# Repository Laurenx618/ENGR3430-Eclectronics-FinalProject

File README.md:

# ENGR3430-Eclectronics-FinalProject

## Description

This project is for the Eclectronics Final.

The final layout used was `no_connector`.

Here, we have a RPI2040 to connect to an ESP32-WROOM-32 (just for WIFI use) as well as an LCD screen in order to  connect to the internet, read someone's *Now Playing* information using the Spotify API Spotipy, and display the song on the screen. There is also a circuit for light detection, which is used to create a "light" and "dark" mode on screen. All of these are communicating with the RPI2040.

----
## Hardware Connections

* Microcontroller: RPI2040
* WiFi Module: ESP32-WROOM-32
* LCD Screen: 16x2 Serial LCD [(Amazon Link)](https://www.amazon.com/HiLetgo-HD44780-I2C1602-Interface-Backlight/dp/B07W5KC65S)

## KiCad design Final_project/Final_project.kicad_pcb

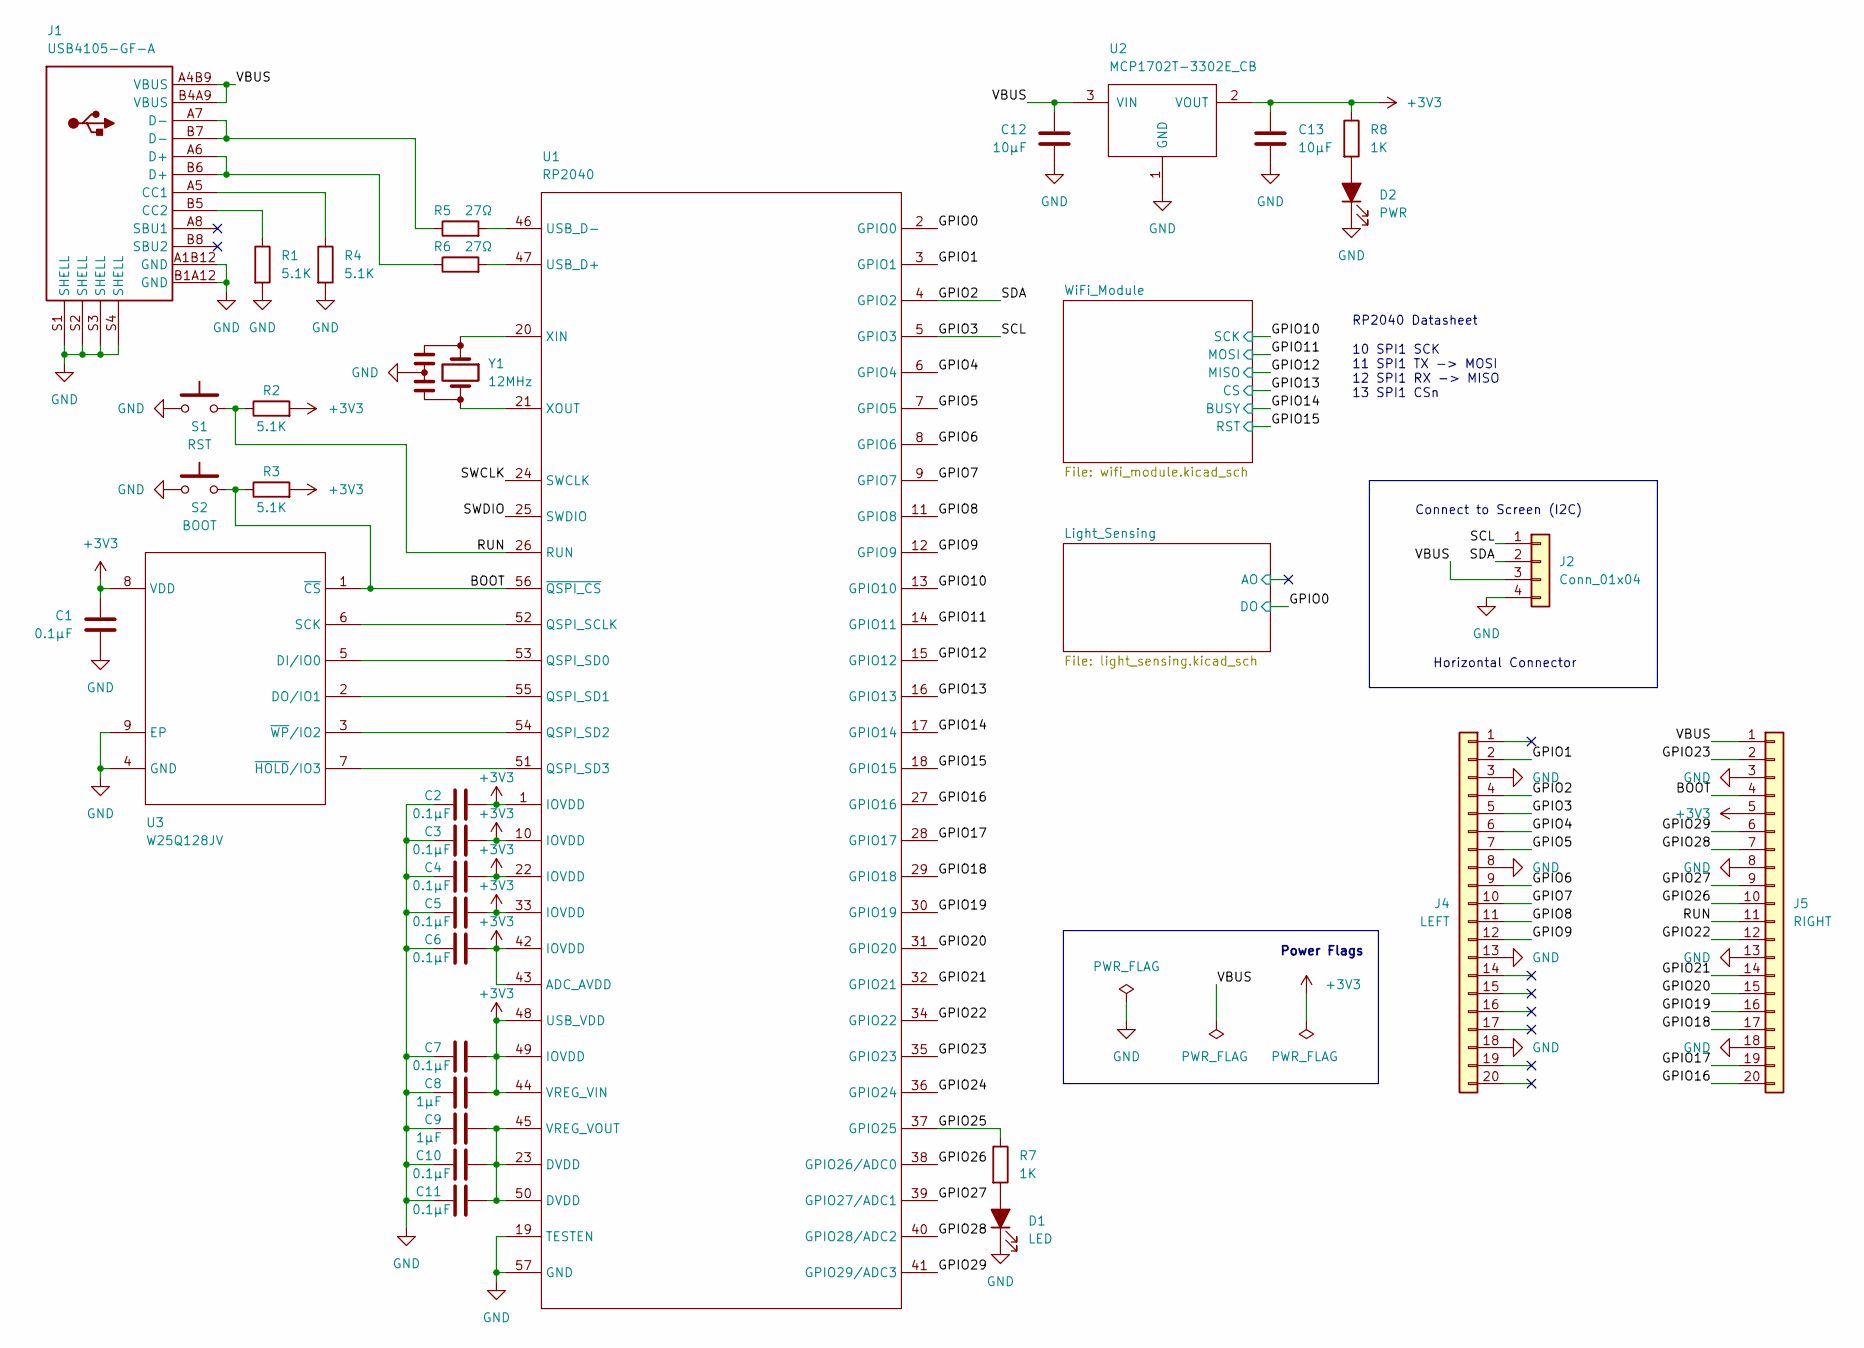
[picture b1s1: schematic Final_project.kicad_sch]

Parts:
C1, C2, C3: 0.1µF; C_0603_1608Metric; Digi-Key_Part CL10B104JB8NNNC
C4, C5, C6, C7, C10, C11: 0.1µF; C_0603_1608Metric
C8: 1µF; C_0603_1608Metric; Digi-Key_Part CL10B105KA8NNNC
C9: 1µF; C_0603_1608Metric
C12, C13: 10µF; C_0603_1608Metric; Digi-Key_Part GRM188R61E106KA73D
D1: LED; LTST-C170TBKT
D2: PWR; LTST-C170TGKT
J1: USB4105-GF-A
J2: Conn_01x04; PinSocket_1x04_P2.54mm_Horizontal
J4: LEFT; PinSocket_1x20_P2.54mm_Vertical
J5: RIGHT; PinSocket_1x20_P2.54mm_Vertical
R1: 5.1K; R_0603_1608Metric
R2, R4: 5.1K; R_0603_1608Metric; Digi-Key_Part ERJ-3EKF5101V
R3: 5.1K; R_0603_1608Metric; Digi-Key_Part ERJ-3EKF5101VERJ-3EKF5101V
R5: 27Ω; R_0603_1608Metric; Part RC0603FR-071KL
R6: 27Ω; R_0603_1608Metric
R7, R8: 1K; R_0603_1608Metric; Digi-Key_Part RC0603FR-071KL
S1: RST; KXT321LHS
S2: BOOT; KXT321LHS
U1: RP2040
U2: MCP1702T-3302E_CB; MCP1702T-3302E&slash_CB
U3: W25Q128JV; MIC_WSON-8-M
Y1: 12MHz; CSTNE

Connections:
+3V3: C1.2, C2.1, C3.1, C4.1, C5.1, C6.1, C7.1, C8.1, C13.1, J5.5, R2.2, R3.2, R8.1, U1.1 (IOVDD), U1.10 (IOVDD), U1.22 (IOVDD), U1.33 (IOVDD), U1.42 (IOVDD), U1.43 (ADC_AVDD), U1.44 (VREG_VIN), U1.48 (USB_VDD), U1.49 (IOVDD), U2.2 (VOUT), U3.8 (VDD); also elsewhere on the board
/BOOT: J5.4, R3.1, S2.2, U1.56 (~QSPI_CS), U3.1 (~CS)
/GPIO0: U1.2 (GPIO0); also elsewhere on the board
/GPIO1: J4.2, U1.3 (GPIO1)
/GPIO2: J2.2, J4.4, U1.4 (GPIO2)
/GPIO3: J2.1, J4.5, U1.5 (GPIO3)
/GPIO4: J4.6, U1.6 (GPIO4)
/GPIO5: J4.7, U1.7 (GPIO5)
/GPIO6: J4.9, U1.8 (GPIO6)
/GPIO7: J4.10, U1.9 (GPIO7)
/GPIO8: J4.11, U1.11 (GPIO8)
/GPIO9: J4.12, U1.12 (GPIO9)
/GPIO10: U1.13 (GPIO10); also elsewhere on the board
/GPIO11: U1.14 (GPIO11); also elsewhere on the board
/GPIO12: U1.15 (GPIO12); also elsewhere on the board
/GPIO13: U1.16 (GPIO13); also elsewhere on the board
/GPIO14: U1.17 (GPIO14); also elsewhere on the board
/GPIO15: U1.18 (GPIO15); also elsewhere on the board
/GPIO16: J5.20, U1.27 (GPIO16)
/GPIO17: J5.19, U1.28 (GPIO17)
/GPIO18: J5.17, U1.29 (GPIO18)
/GPIO19: J5.16, U1.30 (GPIO19)
/GPIO20: J5.15, U1.31 (GPIO20)
/GPIO21: J5.14, U1.32 (GPIO21)
/GPIO22: J5.12, U1.34 (GPIO22)
/GPIO23: J5.2, U1.35 (GPIO23)
/GPIO24: U1.36 (GPIO24)
/GPIO25: R7.1, U1.37 (GPIO25)
/GPIO26: J5.10, U1.38 (GPIO26/ADC0)
/GPIO27: J5.9, U1.39 (GPIO27/ADC1)
/GPIO28: J5.7, U1.40 (GPIO28/ADC2)
/GPIO29: J5.6, U1.41 (GPIO29/ADC3)
/RUN: J5.11, R2.1, S1.2, U1.26 (RUN)
/SWCLK: U1.24 (SWCLK)
/SWDIO: U1.25 (SWDIO)
/VBUS: C12.2, J1.A4B9 (VBUS), J1.B4A9 (VBUS), J2.3, J5.1, U2.3 (VIN)
GND: C1.1, C2.2, C3.2, C4.2, C5.2, C6.2, C7.2, C8.2, C9.2, C10.2, C11.2, C12.1, C13.2, D1.1 (K), D2.1 (K), J1.A1B12 (GND), J1.B1A12 (GND), J1.S1 (SHELL), J1.S2 (SHELL), J1.S3 (SHELL), J1.S4 (SHELL), J2.4, J4.3, J4.8, J4.13, J4.18, J5.3, J5.8, J5.13, J5.18, R1.2, R4.2, S1.1, S2.1, U1.19 (TESTEN), U1.57 (GND), U2.1 (GND), U3.4 (GND), U3.9 (EP), Y1.2; also elsewhere on the board
unnamed: C9.1, C10.1, C11.1, U1.23 (DVDD), U1.45 (VREG_VOUT), U1.50 (DVDD)
unnamed: D1.2 (A), R7.2
unnamed: D2.2 (A), R8.2
unnamed: J1.A5 (CC1), R4.1
unnamed: J1.A6 (D+), J1.B6 (D+), R6.1
unnamed: J1.A7 (D-), J1.B7 (D-), R5.1
unnamed: J1.B5 (CC2), R1.1
unnamed: R5.2, U1.46 (USB_D-)
unnamed: R6.2, U1.47 (USB_D+)
unnamed: U1.20 (XIN), Y1.1
unnamed: U1.21 (XOUT), Y1.3
unnamed: U1.51 (QSPI_SD3), U3.7 (~HOLD/IO3)
unnamed: U1.52 (QSPI_SCLK), U3.6 (SCK)
unnamed: U1.53 (QSPI_SD0), U3.5 (DI/IO0)
unnamed: U1.54 (QSPI_SD2), U3.3 (~WP/IO2)
unnamed: U1.55 (QSPI_SD1), U3.2 (DO/IO1)

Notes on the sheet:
Connect to Screen (I2C)
Horizontal Connector
Power Flags
RP2040 Datasheet 10 SPI1 SCK 11 SPI1 TX -> MOSI 12 SPI1 RX -> MISO 13 SPI1 CSn

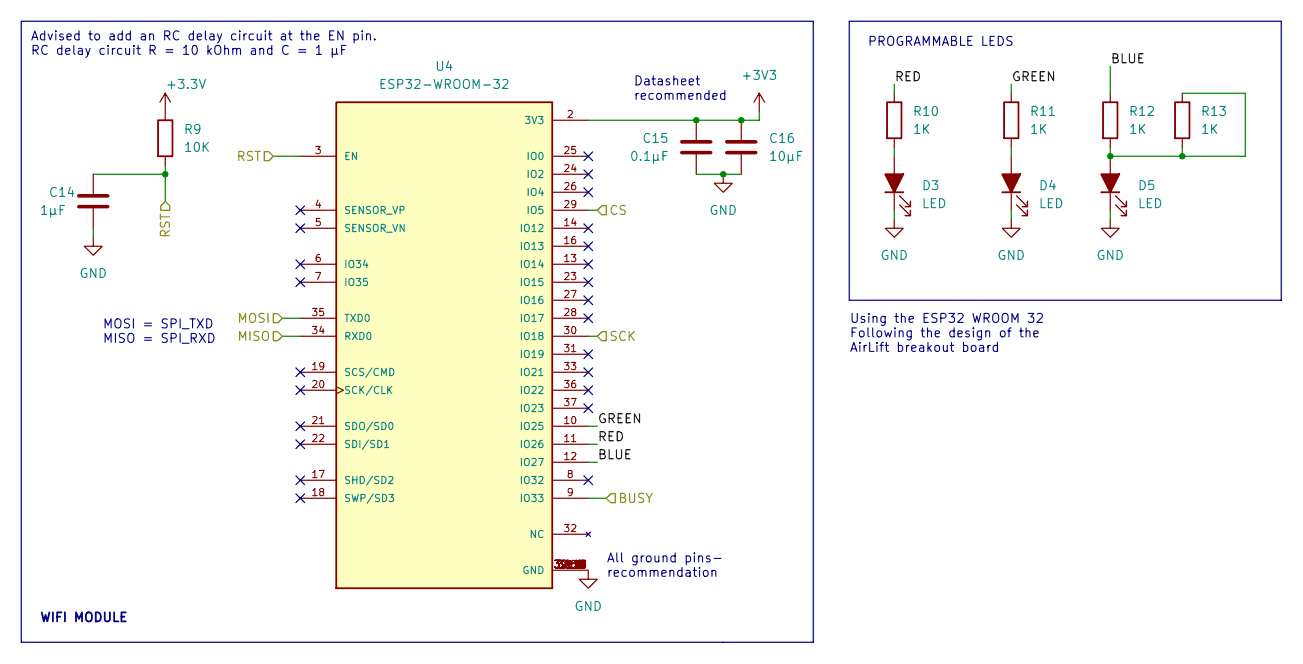
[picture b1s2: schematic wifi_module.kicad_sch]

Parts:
C14: 1µF; C_0603_1608Metric; Digi-Key_Part CL10B105KA8NNNC
C15: 0.1µF; C_0603_1608Metric; Digi-Key_Part CL10B105KA8NNNC
C16: 10µF; C_0603_1608Metric; Digi-Key_Part GRM188R61E106KA73D
D3, D4, D5: LED; LTST-C170TBKT
R9: 10K; R_0805_2012Metric
R10, R11, R12: 1K; R_0603_1608Metric; Digi-Key_Part RC0603FR-071KL
R13: 1K; R_0603_1608Metric
U4: ESP32-WROOM-32; MODULE_ESP32-WROOM-32; PARTREV 2.9

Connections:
+3.3V: R9.1
+3V3: C15.1, C16.1, U4.2 (3V3); also elsewhere on the board
/GPIO10: U4.30 (IO18); also elsewhere on the board
/GPIO11: U4.35 (TXD0); also elsewhere on the board
/GPIO12: U4.34 (RXD0); also elsewhere on the board
/GPIO13: U4.29 (IO5); also elsewhere on the board
/GPIO14: U4.9 (IO33); also elsewhere on the board
/GPIO15: C14.2, R9.2, U4.3 (EN); also elsewhere on the board
/WiFi_Module/BLUE: R12.1, U4.12 (IO27)
/WiFi_Module/GREEN: R11.1, U4.10 (IO25)
/WiFi_Module/RED: R10.1, U4.11 (IO26)
GND: C14.1, C15.2, C16.2, D3.1 (K), D4.1 (K), D5.1 (K), U4.1 (GND), U4.15 (GND), U4.38 (GND), U4.39_1 (GND), U4.39_2 (GND), U4.39_3 (GND), U4.39_4 (GND), U4.39_5 (GND), U4.39_6 (GND), U4.39_7 (GND), U4.39_8 (GND), U4.39_9 (GND), U4.39_10 (GND), U4.39_11 (GND), U4.39_12 (GND), U4.39_13 (GND), U4.39_14 (GND), U4.39_15 (GND), U4.39_16 (GND), U4.39_17 (GND), U4.39_18 (GND), U4.39_19 (GND), U4.39_20 (GND), U4.39_21 (GND); also elsewhere on the board
unnamed: D3.2 (A), R10.2
unnamed: D4.2 (A), R11.2
unnamed: D5.2 (A), R12.2, R13.1, R13.2

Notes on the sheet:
PROGRAMMABLE LEDS
WIFI MODULE
All ground pins- recommendation
Datasheet recommended
MOSI = SPI_TXD MISO = SPI_RXD
Using the ESP32 WROOM 32 Following the design of the AirLift breakout board
Advised to add an RC delay circuit at the EN pin. RC delay circuit R = 10 kOhm and C = 1 μF

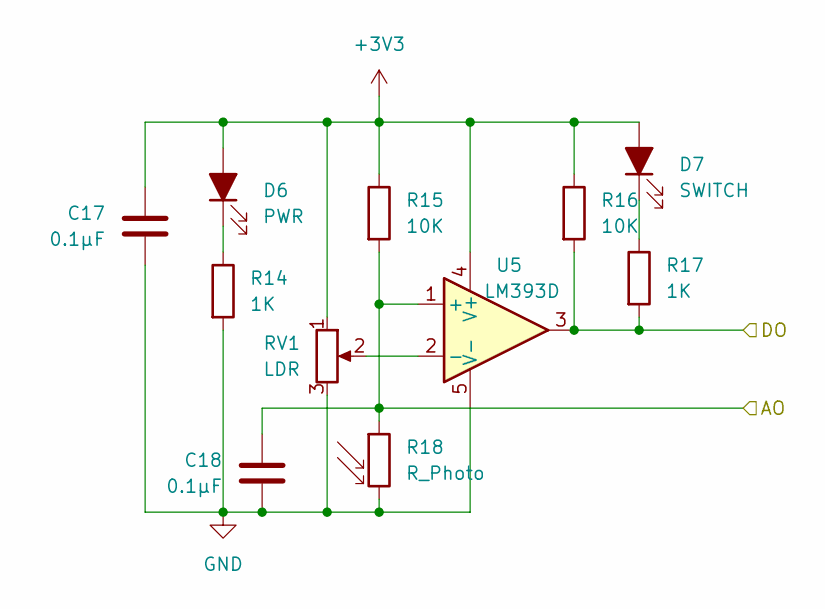
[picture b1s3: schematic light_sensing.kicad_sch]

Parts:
C17, C18: 0.1µF; C_0603_1608Metric; Digi-Key_Part CL10B104JB8NNNC
D6: PWR; LTST-C170TGKT
D7: SWITCH; LTST-C170TGKT
R14, R17: 1K; R_0603_1608Metric; Digi-Key_Part RC0603FR-071KL
R15, R16: 10K; R_0805_2012Metric
R18: R_Photo; 02-LDR4
RV1: LDR; TRIM_T73YU103KT20
U5: LM393D

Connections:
+3V3: C17.2, D6.2 (A), D7.2 (A), R15.1, R16.1, RV1.1, U5.4 (V+); also elsewhere on the board
/GPIO0: R16.2, R17.2, U5.3; also elsewhere on the board
/Light_Sensing/AO: C18.2, R15.2, R18.1, U5.1 (+)
GND: C17.1, C18.1, R14.2, R18.2, RV1.3, U5.5 (V-); also elsewhere on the board
unnamed: D6.1 (K), R14.1
unnamed: D7.1 (K), R17.1
unnamed: RV1.2, U5.2 (-)

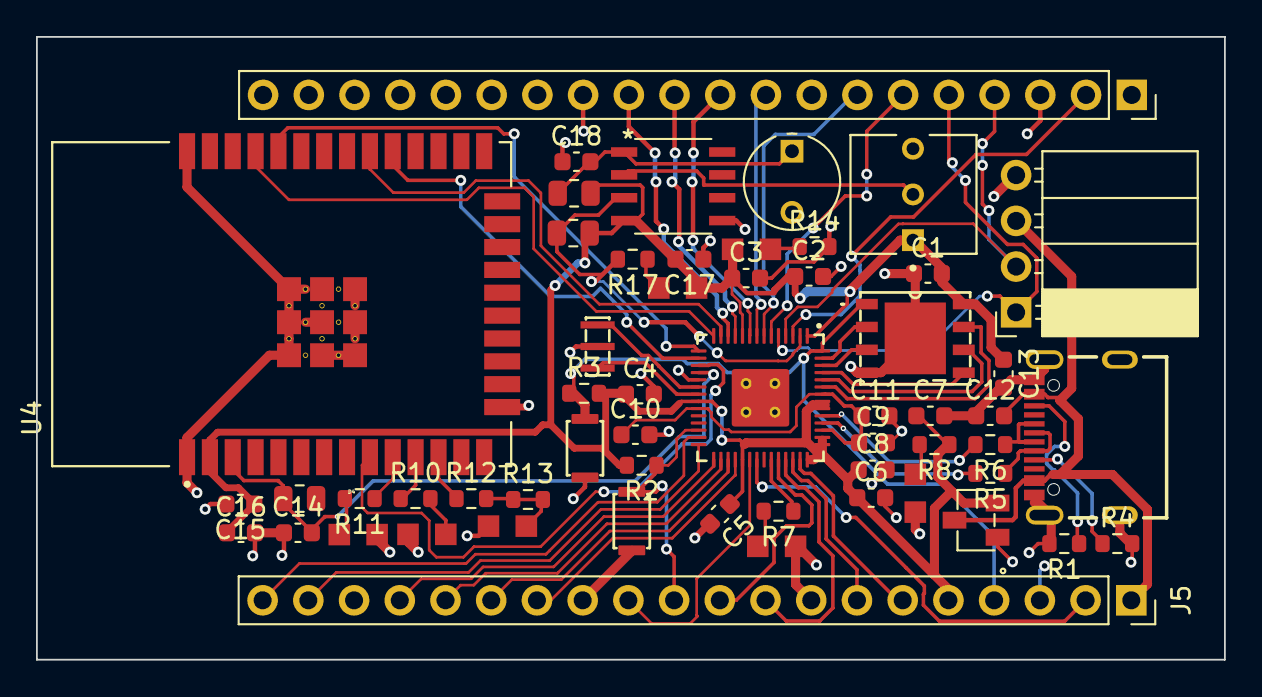
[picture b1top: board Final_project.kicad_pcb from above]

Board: 2 copper layers, 66.0 x 34.6 mm, 56 parts (0 on the bottom side), 60 nets.

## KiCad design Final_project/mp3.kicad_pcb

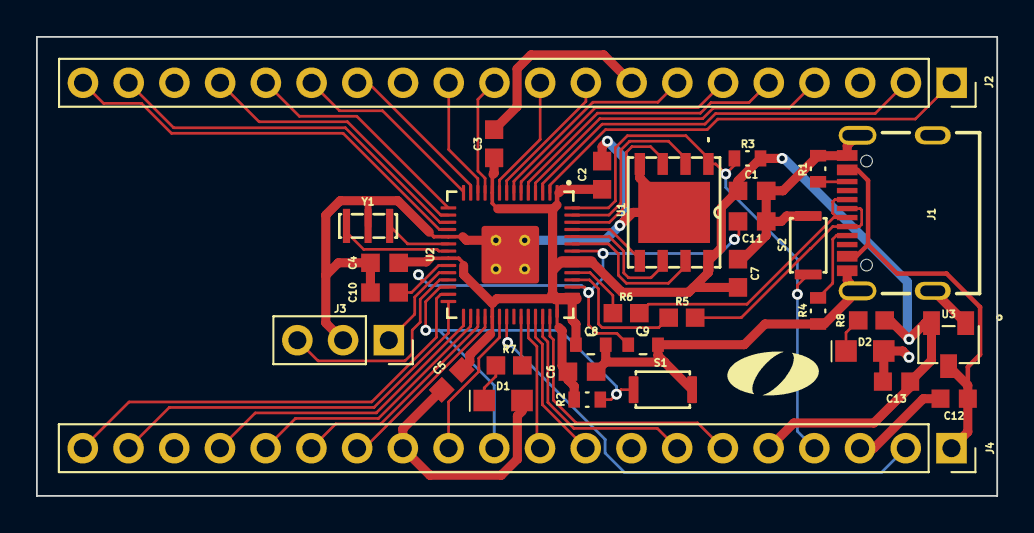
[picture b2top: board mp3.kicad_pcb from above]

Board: 2 copper layers, 53.3 x 25.5 mm, 34 parts (0 on the bottom side), 52 nets.

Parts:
C1, C2, C3, C4, C5, C6, C7, C10, C11: 0.1µF; CL10B104JB8NNNC
C8, C9: 1µF; CL10B105KA8NNNC
C12, C13: 10µF; GRM188R61E106KA73D
D1: LED; LTST-C170TBKT
D2: PWR; LTST-C170TGKT
J1: USB4105-GF-A
J2: LEFT; PinSocket_1x20_P2.54mm_Vertical
J3: DEBUG; PinSocket_1x03_P2.54mm_Vertical
J4: RIGHT; PinSocket_1x20_P2.54mm_Vertical
OlinLogoSm: G***; OlinLogoSm
R1, R2, R3, R4: 5.1K; RES_ERJ3EKF5101V
R5, R6: 27Ω; RC0603FR-071KL
R7, R8: 1K; RC0603FR-071KL
S1: RST; KXT321LHS
S2: BOOT; KXT321LHS
U1: W25Q128JV; MIC_WSON-8-M
U2: RP2040
U3: MCP1702T-3302E_CB; MCP1702T-3302E&slash_CB
Y1: 12MHz; CSTNE

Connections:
+3V3: C1.2, C2.1, C3.1, C4.1, C5.1, C6.1, C7.1, C8.1, C13.1, J4.5, R2.2, R3.2, R8.1, U1.8 (VDD), U2.1 (IOVDD), U2.10 (IOVDD), U2.22 (IOVDD), U2.33 (IOVDD), U2.42 (IOVDD), U2.43 (ADC_AVDD), U2.44 (VREG_VIN), U2.48 (USB_VDD), U2.49 (IOVDD), U3.2 (VOUT)
/BOOT: J4.4, R3.1, S2.2, U1.1 (~CS), U2.56 (~QSPI_CS)
/GPIO0: J2.1, U2.2 (GPIO0)
/GPIO1: J2.2, U2.3 (GPIO1)
/GPIO2: J2.4, U2.4 (GPIO2)
/GPIO3: J2.5, U2.5 (GPIO3)
/GPIO4: J2.6, U2.6 (GPIO4)
/GPIO5: J2.7, U2.7 (GPIO5)
/GPIO6: J2.9, U2.8 (GPIO6)
/GPIO7: J2.10, U2.9 (GPIO7)
/GPIO8: J2.11, U2.11 (GPIO8)
/GPIO9: J2.12, U2.12 (GPIO9)
/GPIO10: J2.14, U2.13 (GPIO10)
/GPIO11: J2.15, U2.14 (GPIO11)
/GPIO12: J2.16, U2.15 (GPIO12)
/GPIO13: J2.17, U2.16 (GPIO13)
/GPIO14: J2.19, U2.17 (GPIO14)
/GPIO15: J2.20, U2.18 (GPIO15)
/GPIO16: J4.20, U2.27 (GPIO16)
/GPIO17: J4.19, U2.28 (GPIO17)
/GPIO18: J4.17, U2.29 (GPIO18)
/GPIO19: J4.16, U2.30 (GPIO19)
/GPIO20: J4.15, U2.31 (GPIO20)
/GPIO21: J4.14, U2.32 (GPIO21)
/GPIO22: J4.12, U2.34 (GPIO22)
/GPIO23: J4.2, U2.35 (GPIO23)
/GPIO25: R7.1, U2.37 (GPIO25)
/GPIO26: J4.10, U2.38 (GPIO26/ADC0)
/GPIO27: J4.9, U2.39 (GPIO27/ADC1)
/GPIO28: J4.7, U2.40 (GPIO28/ADC2)
/GPIO29: J4.6, U2.41 (GPIO29/ADC3)
/RUN: J4.11, R2.1, S1.2, U2.26 (RUN)
/SWCLK: J3.1, U2.24 (SWCLK)
/SWDIO: J3.3, U2.25 (SWDIO)
/VBUS: C12.2, J1.A4B9 (VBUS), J1.B4A9 (VBUS), J4.1, U3.3 (VIN)
GND: C1.1, C2.2, C3.2, C4.2, C5.2, C6.2, C7.2, C8.2, C9.2, C10.2, C11.2, C12.1, C13.2, D1.1 (K), D2.1 (K), J1.A1B12 (GND), J1.B1A12 (GND), J1.S1 (SHELL), J1.S2 (SHELL), J1.S3 (SHELL), J1.S4 (SHELL), J2.3, J2.8, J2.13, J2.18, J3.2, J4.3, J4.8, J4.13, J4.18, R1.2, R4.2, S1.1, S2.1, U1.4 (GND), U1.9 (EP), U2.19 (TESTEN), U2.57 (GND), U3.1 (GND), Y1.2
unnamed: C9.1, C10.1, C11.1, U2.23 (DVDD), U2.45 (VREG_VOUT), U2.50 (DVDD)
unnamed: D1.2 (A), R7.2
unnamed: D2.2 (A), R8.2
unnamed: J1.A5 (CC1), R4.1
unnamed: J1.A6 (D+), J1.B6 (D+), R6.1
unnamed: J1.A7 (D-), J1.B7 (D-), R5.1
unnamed: J1.B5 (CC2), R1.1
unnamed: R5.2, U2.46 (USB_D-)
unnamed: R6.2, U2.47 (USB_D+)
unnamed: U1.2 (DO/IO1), U2.55 (QSPI_SD1)
unnamed: U1.3 (~WP/IO2), U2.54 (QSPI_SD2)
unnamed: U1.5 (DI/IO0), U2.53 (QSPI_SD0)
unnamed: U1.6 (SCK), U2.52 (QSPI_SCLK)
unnamed: U1.7 (~HOLD/IO3), U2.51 (QSPI_SD3)
unnamed: U2.20 (XIN), Y1.1
unnamed: U2.21 (XOUT), Y1.3

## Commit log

2022-11-16 Add library and hierarchical schematic
2022-11-16 added audiojack
2022-11-18 Complete wifi module airlift
2022-11-18 Complete pinouts on main
2022-11-18 assigned footprints to audiojack caps
2022-11-18 Add light sensing sheet
2022-11-26 Add miniproj parts, begin photosensing circuit
2022-11-26 added copy of light sensing module
2022-11-27 Add pinouts for connectors
2022-11-27 added a footprint to the current library and uploaded Micropython_code
2022-11-27 Add horizontal pin connect
2022-11-28 started layout
2022-11-28 Fix 3V3 label, fix USB footprint, layout begin
2022-11-28 Layout continued, delete header
2022-11-28 almost finished layout
2022-11-28 fixed several unrouted problems, now there are 3 left
2022-11-28 updated pcb file
2022-11-28 finishing up layout, a few steps remained
2022-11-29 Add 3d, fixing vias and layout issues
2022-11-29 fixed several problems
2022-11-29 rewired some GND pins
2022-11-29 Add final layout with no connector
2022-11-30 Clean layout and ESP32 footprint
2022-11-30 Fix trace sizing power
2022-11-30 Complete layout for no connectors add silkscreens
2022-12-20 Upload code from RPI, add description
2022-12-20 Update README for code
2022-12-20 Update main README
2022-12-20 Extra note to README

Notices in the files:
parts and their libraries:
Copyright 2021 Accelerated Designs. All rights reserved.
